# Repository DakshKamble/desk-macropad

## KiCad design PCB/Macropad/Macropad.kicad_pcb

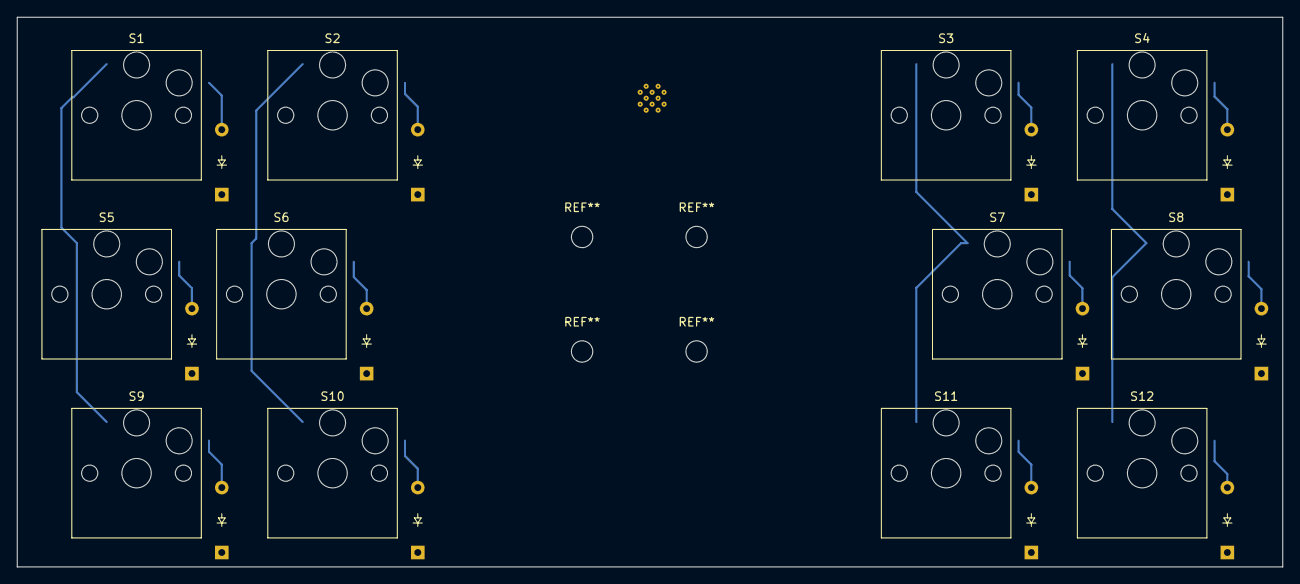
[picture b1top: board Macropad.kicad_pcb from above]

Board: 2 copper layers, 148.5 x 64.5 mm, 25 parts (1 on the bottom side), 22 nets.

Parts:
D1, D2, D3, D4, D5, D6, D7, D8, D9, D10, D11, D12: Diode_DO-35
S1, S2, S3, S4, S5, S6, S7, S8, S9, S10, S11, S12: Hotswap_Choc_V1
U1: ESP32-S3-WROOM-1

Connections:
/Macropad/IO1: U1.38 (IO2), U1.39 (IO1)
/Macropad/IO4: S1.1, S5.1, S9.1, U1.4 (IO4)
/Macropad/IO5: S2.1, S6.1, S10.1, U1.5 (IO5)
/Macropad/IO6: S3.1, S7.1, S11.1, U1.6 (IO6)
/Macropad/IO7: S4.1, S8.1, S12.1, U1.7 (IO7)
/Macropad/IO8: D1.1 (K), D2.1 (K), D3.1 (K), D4.1 (K), U1.12 (IO8)
/Macropad/IO9: D5.1 (K), D6.1 (K), D7.1 (K), D8.1 (K), U1.17 (IO9)
/Macropad/IO10: D9.1 (K), D10.1 (K), D11.1 (K), D12.1 (K), U1.18 (IO10)
GND: U1.1 (GND), U1.40 (GND), U1.41 (GND)
IO38: U1.31 (IO38), U1.32 (IO39)
unnamed: D1.2 (A), S1.2
unnamed: D2.2 (A), S2.2
unnamed: D3.2 (A), S3.2
unnamed: D4.2 (A), S4.2
unnamed: D5.2 (A), S5.2
unnamed: D6.2 (A), S6.2
unnamed: D7.2 (A), S7.2
unnamed: D8.2 (A), S8.2
unnamed: D9.2 (A), S9.2
unnamed: D10.2 (A), S10.2
unnamed: D11.2 (A), S11.2
unnamed: D12.2 (A), S12.2

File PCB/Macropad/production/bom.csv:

Designator,Footprint,Quantity,Value,LCSC Part #
"S1, S10, S11, S12, S2, S3, S4, S5, S6, S7, S8, S9",Hotswap_Choc_V1,12,~,
U1,ESP32-S3-WROOM-1,1,ESP32-S3-WROOM-1,
